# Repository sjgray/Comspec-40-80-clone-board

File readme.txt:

Comspec 40/80-S2 board Clone
============================

This is a clone of the Comspec 40/80 S2 board for PET/CBM computers.
This board allows the PET to switch between real 40 or 80 column video modes.
Whe the board is switched the computer is reset. These boards were supplied
with both 40 and 80 column Editor ROMs combined into a single EPROM. A wire
from the Comspec board to the upper address pin of the EPROM automatically
selected the correct ROM for the selected video mode.

More information can be found on the web:
http://www.6502.org/users/sjgray/projects/cbm4080/index.html

Steve

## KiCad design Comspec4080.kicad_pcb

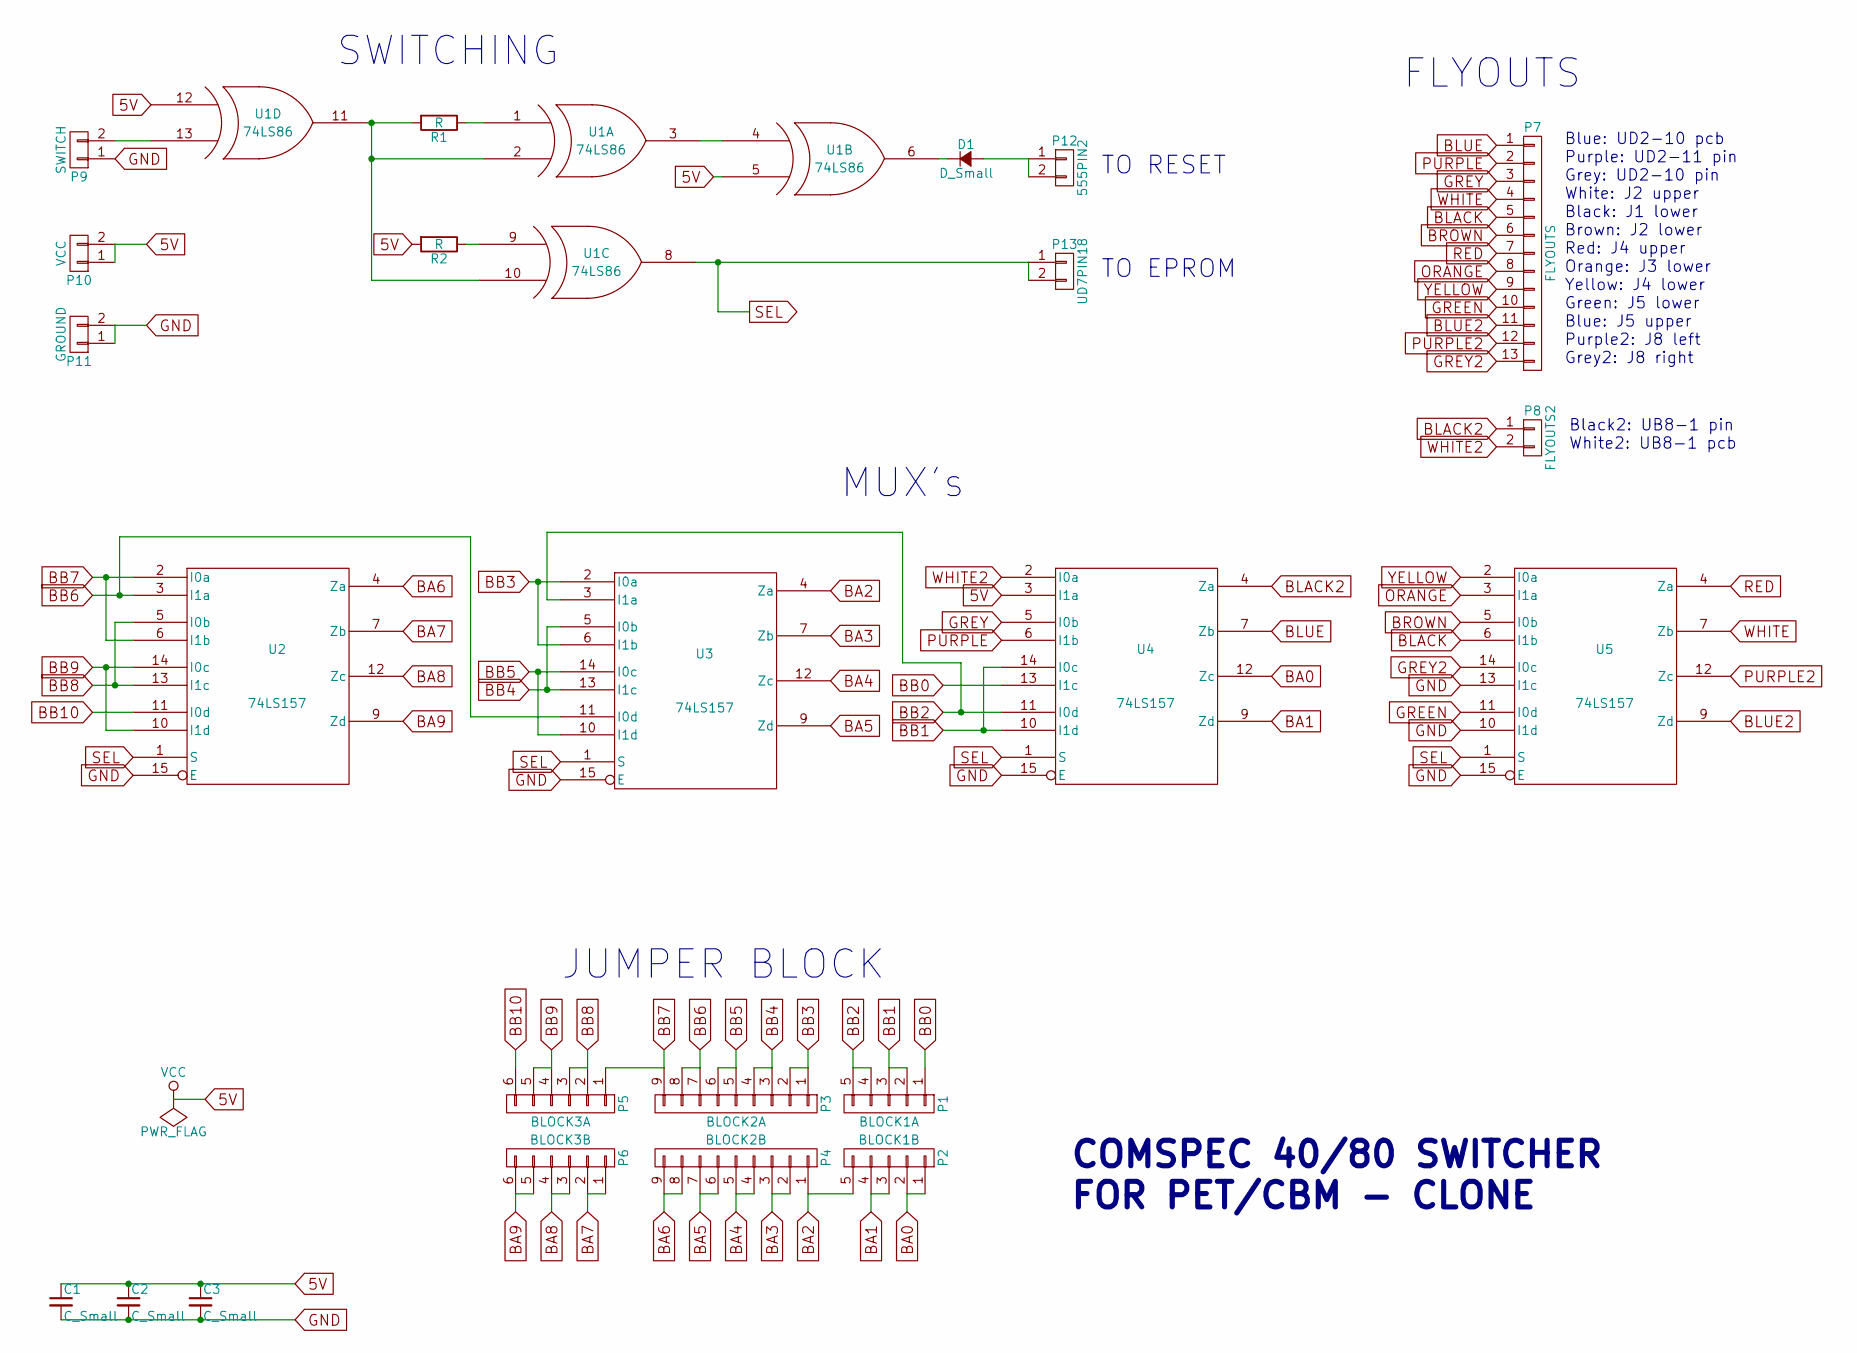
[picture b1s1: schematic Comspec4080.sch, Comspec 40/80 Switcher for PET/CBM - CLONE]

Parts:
C1, C2, C3: C_Small; C_Disc_D3.0mm_W1.6mm_P2.50mm
D1: D_Small; D_A-405_P7.62mm_Horizontal
P1: BLOCK1A; Pin_Header_Straight_1x05_Pitch2.54mm
P2: BLOCK1B; Pin_Header_Straight_1x05_Pitch2.54mm
P3: BLOCK2A; Pin_Header_Straight_1x09_Pitch2.54mm
P4: BLOCK2B; Pin_Header_Straight_1x09_Pitch2.54mm
P5: BLOCK3A; Pin_Header_Straight_1x06_Pitch2.54mm
P6: BLOCK3B; Pin_Header_Straight_1x06_Pitch2.54mm
P7: FLYOUTS; Pin_Header_Straight_1x13_Pitch2.54mm
P8: FLYOUTS2; Pin_Header_Straight_1x02_Pitch2.54mm
P9: SWITCH; Pin_Header_Straight_1x02_Pitch2.54mm
P10: VCC; Pin_Header_Straight_1x02_Pitch2.54mm
P11: GROUND; Pin_Header_Straight_1x02_Pitch2.54mm
P12: 555PIN2; Pin_Header_Straight_1x02_Pitch2.54mm
P13: UD7PIN18; Pin_Header_Straight_1x02_Pitch2.54mm
R1, R2: R; R_Axial_DIN0207_L6.3mm_D2.5mm_P7.62mm_Horizontal
U1: 74LS86; DIP-14_W7.62mm_LongPads
U2, U3, U4, U5: 74LS157; DIP-16_W7.62mm_LongPads

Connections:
5V: C1.1, C2.1, C3.1, P10.1, P10.2, R2.2, U1.5 (IN2), U1.12 (IN1), U1.14 (VCC), U2.16 (VCC), U3.16 (VCC), U4.3 (I1a), U4.16 (VCC), U5.16 (VCC)
BA0: P2.1, P2.2, U4.12 (Zc)
BA1: P2.3, P2.4, U4.9 (Zd)
BA2: P2.5, P4.1, U3.4 (Za)
BA3: P4.2, P4.3, U3.7 (Zb)
BA4: P4.4, P4.5, U3.12 (Zc)
BA5: P4.6, P4.7, U3.9 (Zd)
BA6: P4.8, P4.9, U2.4 (Za)
BA7: P6.1, P6.2, U2.7 (Zb)
BA8: P6.3, P6.4, U2.12 (Zc)
BA9: P6.5, P6.6, U2.9 (Zd)
BB0: P1.1, U4.13 (I1c)
BB1: P1.2, P1.3, U4.10 (I1d), U4.14 (I0c)
BB2: P1.4, P1.5, U3.3 (I1a), U4.11 (I0d)
BB3: P3.1, P3.2, U3.2 (I0a), U3.6 (I1b)
BB4: P3.3, P3.4, U3.5 (I0b), U3.13 (I1c)
BB5: P3.5, P3.6, U3.10 (I1d), U3.14 (I0c)
BB6: P3.7, P3.8, U2.3 (I1a), U3.11 (I0d)
BB7: P3.9, P5.1, U2.2 (I0a), U2.6 (I1b)
BB8: P5.2, P5.3, U2.5 (I0b), U2.13 (I1c)
BB9: P5.4, P5.5, U2.10 (I1d), U2.14 (I0c)
BB10: P5.6, U2.11 (I0d)
BLACK: P7.5, U5.6 (I1b)
BLACK2: P8.1, U4.4 (Za)
BLUE: P7.1, U4.7 (Zb)
BLUE2: P7.11, U5.9 (Zd)
BROWN: P7.6, U5.5 (I0b)
GND: C1.2, C2.2, C3.2, P9.1, P11.1, P11.2, U1.7 (GND), U2.8 (GND), U2.15 (E), U3.8 (GND), U3.15 (E), U4.8 (GND), U4.15 (E), U5.8 (GND), U5.10 (I1d), U5.13 (I1c), U5.15 (E)
GREEN: P7.10, U5.11 (I0d)
GREY: P7.3, U4.5 (I0b)
GREY2: P7.13, U5.14 (I0c)
unnamed: D1.1 (K), U1.6 (OUT)
unnamed: D1.2 (A), P12.1, P12.2
unnamed: P9.2, U1.13 (IN2)
unnamed: R1.1, U1.1 (IN1)
unnamed: R1.2, U1.2 (IN2), U1.10 (IN2), U1.11 (OUT)
unnamed: R2.1, U1.9 (IN1)
unnamed: U1.3 (OUT), U1.4 (IN1)
ORANGE: P7.8, U5.3 (I1a)
PURPLE: P7.2, U4.6 (I1b)
PURPLE2: P7.12, U5.12 (Zc)
RED: P7.7, U5.4 (Za)
SEL: P13.1, P13.2, U1.8 (OUT), U2.1 (S), U3.1 (S), U4.1 (S), U5.1 (S)
WHITE: P7.4, U5.7 (Zb)
WHITE2: P8.2, U4.2 (I0a)
YELLOW: P7.9, U5.2 (I0a)

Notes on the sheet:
COMSPEC 40/80 SWITCHER FOR PET/CBM - CLONE
SWITCHING
FLYOUTS
TO EPROM
TO RESET
JUMPER BLOCK
MUX's
Blue: UD2-10 pcb Purple: UD2-11 pin Grey: UD2-10 pin White: J2 upper Black: J1 lower Brown: J2 lower Red: J4 upper Orange: J3 lower Yellow: J4 lower Green: J5 lower Blue: J5 upper Purple2: J8 left Grey2: J8 right
Black2: UB8-1 pin White2: UB8-1 pcb

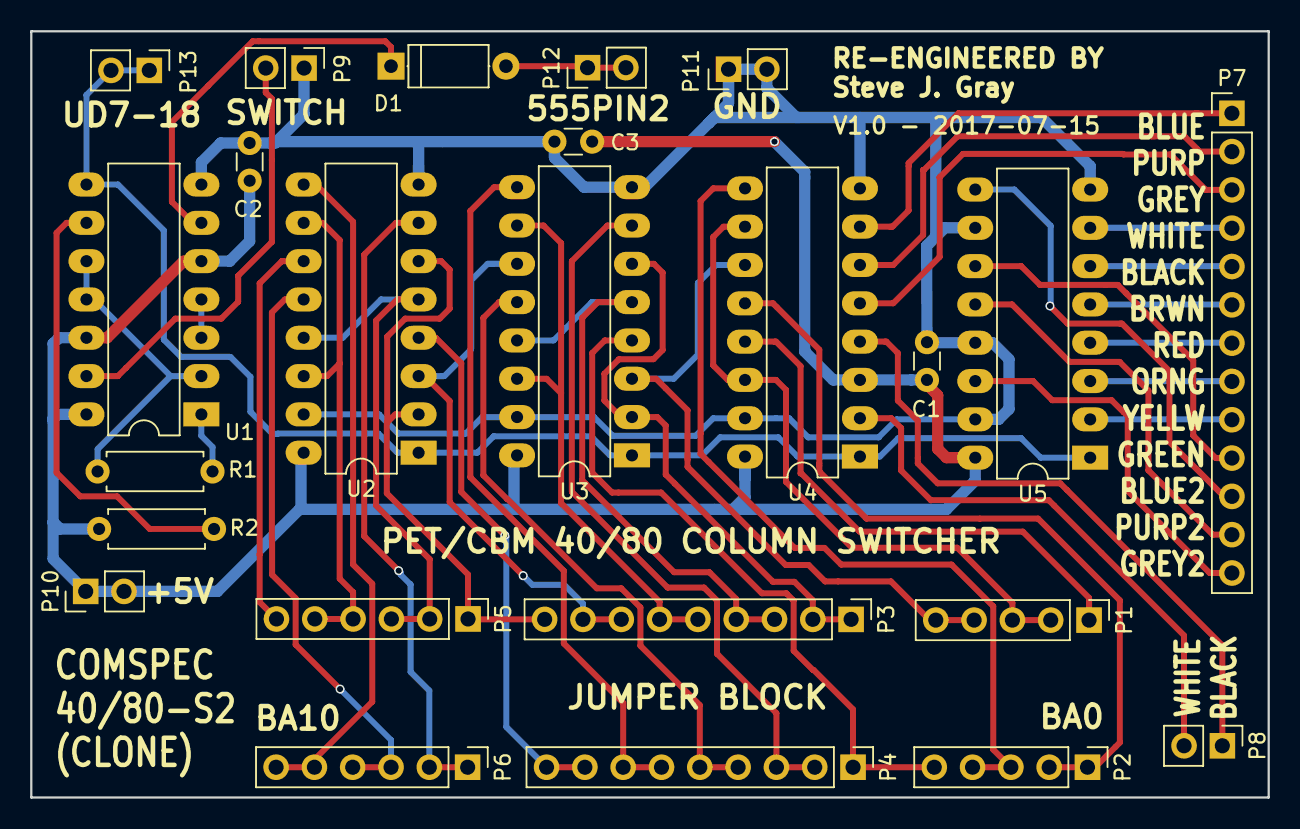
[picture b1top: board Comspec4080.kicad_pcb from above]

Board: 2 copper layers, 82.0 x 50.8 mm, 24 parts (0 on the bottom side), 46 nets.

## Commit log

2021-08-06 :boom::camel: Added .gitattributes & .gitignore files
2021-08-06 Initial commit
    Clone of the Comspec 40/80-S2 adapter for PET/CBM computer.
    Allows switching between 40 and 80 column video mode with a single
    switch. Also switches the EditROM.
